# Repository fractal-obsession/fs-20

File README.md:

# FS-20

MS-20 like eurorack filter mopdule based on [KS-20](https://kassu2000.blogspot.com/2019/07/ks-20-filter.html) by _kassutronics_ based on the schematic published by René Schmitz.

Uses the LM13700 transconductance amplifier and it's buffer stage.

Includes:
 - KiCAD files for PCB and front panel
 - Custom SVGs for front panel footprints
 - JLCPCB-ready fabrication files

There are still some bugs and errors mainly on the front panel, but the electronics are correct.

[follow me](linktr.ee/fractal_obsession), or don't

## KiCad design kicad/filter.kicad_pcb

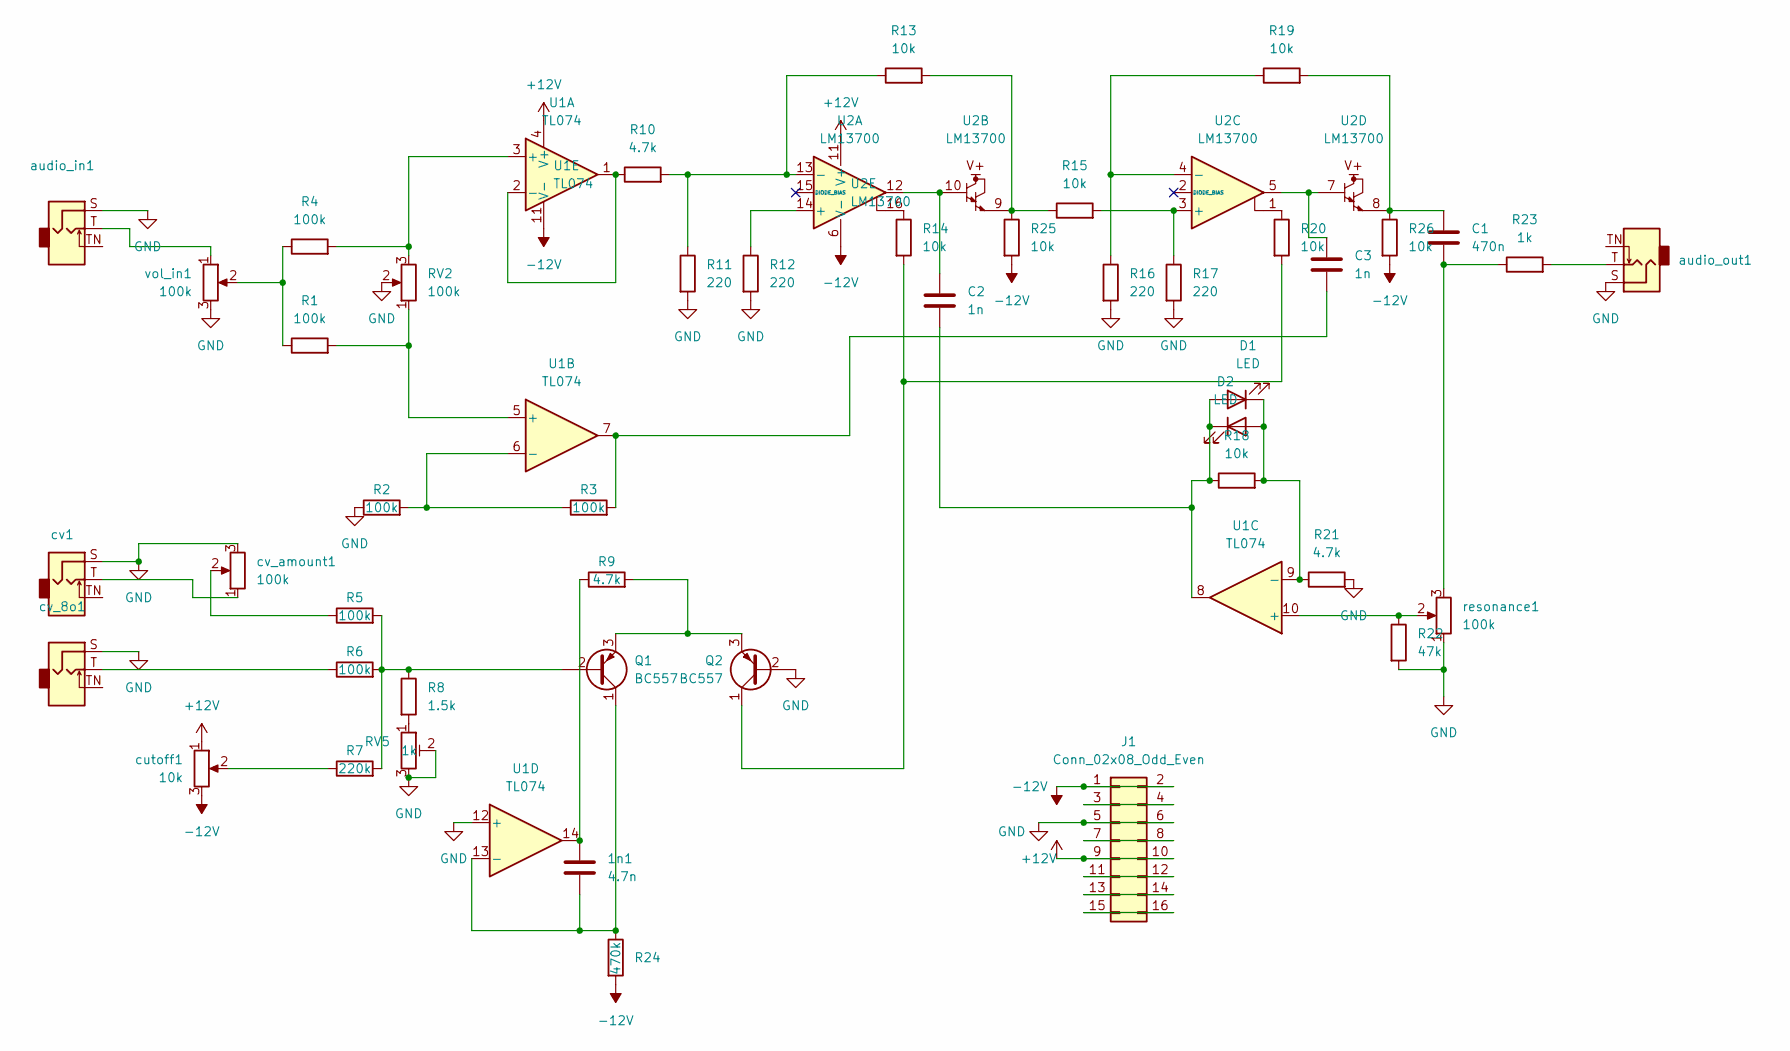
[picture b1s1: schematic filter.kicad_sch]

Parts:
1n1: 4.7n; R_Axial_DIN0207_L6.3mm_D2.5mm_P5.08mm_Vertical
C1: 470n; R_Axial_DIN0207_L6.3mm_D2.5mm_P5.08mm_Vertical
C2, C3: 1n; R_Axial_DIN0207_L6.3mm_D2.5mm_P5.08mm_Vertical
D1, D2: LED; R_Axial_DIN0207_L6.3mm_D2.5mm_P5.08mm_Vertical
J1: Conn_02x08_Odd_Even; PinHeader_2x08_P2.54mm_Vertical
Q1, Q2: BC557; TO-92_Inline
R1, R2, R3, R4, R5, R6: 100k; R_Axial_DIN0207_L6.3mm_D2.5mm_P7.62mm_Horizontal
R7: 220k; R_Axial_DIN0207_L6.3mm_D2.5mm_P7.62mm_Horizontal
R8: 1.5k; R_Axial_DIN0207_L6.3mm_D2.5mm_P7.62mm_Horizontal
R9, R10, R21: 4.7k; R_Axial_DIN0207_L6.3mm_D2.5mm_P7.62mm_Horizontal
R11, R12, R16, R17: 220; R_Axial_DIN0207_L6.3mm_D2.5mm_P7.62mm_Horizontal
R13, R14, R15, R18, R19, R20, R25, R26: 10k; R_Axial_DIN0207_L6.3mm_D2.5mm_P7.62mm_Horizontal
R22: 47k; R_Axial_DIN0207_L6.3mm_D2.5mm_P7.62mm_Horizontal
R23: 1k; R_Axial_DIN0207_L6.3mm_D2.5mm_P7.62mm_Horizontal
R24: 470k; R_Axial_DIN0207_L6.3mm_D2.5mm_P7.62mm_Horizontal
RV2: 100k; Potentiometer_Bourns_PTV09A-1_Single_Vertical
RV5: 1k; Potentiometer_Vishay_T73XX_Horizontal
U1: TL074; DIP-14_W7.62mm_Socket
U2: LM13700; DIP-16_W7.62mm_Socket
audio_in1: AudioJack2_SwitchT; Jack_3.5mm_QingPu_WQP-PJ398SM_Vertical_CircularHoles
audio_out1: AudioJack2_SwitchT; Jack_3.5mm_QingPu_WQP-PJ398SM_Vertical_CircularHoles
cutoff1: 10k; Potentiometer_Bourns_PTV09A-1_Single_Vertical
cv1: AudioJack2_SwitchT; Jack_3.5mm_QingPu_WQP-PJ398SM_Vertical_CircularHoles
cv_8o1: AudioJack2_SwitchT; Jack_3.5mm_QingPu_WQP-PJ398SM_Vertical_CircularHoles
cv_amount1: 100k; Potentiometer_Bourns_PTV09A-1_Single_Vertical
resonance1: 100k; Potentiometer_Bourns_PTV09A-1_Single_Vertical
vol_in1: 100k; Potentiometer_Bourns_PTV09A-1_Single_Vertical

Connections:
+12V: J1.9, J1.10, U1.4 (V+), U2.11 (V+), cutoff1.1
-12V: J1.1, J1.2, R24.2, R25.2, R26.2, U1.11 (V-), U2.6 (V-), cutoff1.3
GND: J1.5, J1.6, Q2.2 (B), R2.1, R11.2, R12.2, R16.2, R17.2, R21.2, R22.2, RV2.2, RV5.2, RV5.3, U1.12 (+), audio_in1.S, audio_out1.S, cv1.S, cv_8o1.S, cv_amount1.3, resonance1.1, vol_in1.3
unnamed: 1n1.1, R9.1, U1.14
unnamed: 1n1.2, Q1.1 (C), R24.1, U1.13 (-)
unnamed: C1.1, R19.2, R26.1, U2.8
unnamed: C1.2, R23.1, resonance1.3
unnamed: C2.1, U2.10, U2.12
unnamed: C2.2, D1.2 (A), D2.1 (K), R18.1, U1.8
unnamed: C3.1, U2.5, U2.7
unnamed: C3.2, R3.2, U1.7
unnamed: D1.1 (K), D2.2 (A), R18.2, R21.1, U1.9 (-)
unnamed: J1.3, J1.4
unnamed: J1.7, J1.8
unnamed: J1.11, J1.12
unnamed: J1.13, J1.14
unnamed: J1.15, J1.16
unnamed: Q1.2 (B), R5.2, R6.2, R7.2, R8.1
unnamed: Q1.3 (E), Q2.3 (E), R9.2
unnamed: Q2.1 (C), R14.2, R20.2
unnamed: R1.1, R4.1, vol_in1.2
unnamed: R1.2, RV2.1, U1.5 (+)
unnamed: R2.2, R3.1, U1.6 (-)
unnamed: R4.2, RV2.3, U1.3 (+)
unnamed: R5.1, cv_amount1.2
unnamed: R6.1, cv_8o1.T
unnamed: R7.1, cutoff1.2
unnamed: R8.2, RV5.1
unnamed: R10.1, U1.1, U1.2 (-)
unnamed: R10.2, R11.1, R13.1, U2.13 (-)
unnamed: R12.1, U2.14 (+)
unnamed: R13.2, R15.1, R25.1, U2.9
unnamed: R14.1, U2.16
unnamed: R15.2, R17.1, U2.3 (+)
unnamed: R16.1, R19.1, U2.4 (-)
unnamed: R20.1, U2.1
unnamed: R22.1, U1.10 (+), resonance1.2
unnamed: R23.2, audio_out1.T
unnamed: audio_in1.T, vol_in1.1
unnamed: cv1.T, cv_amount1.1

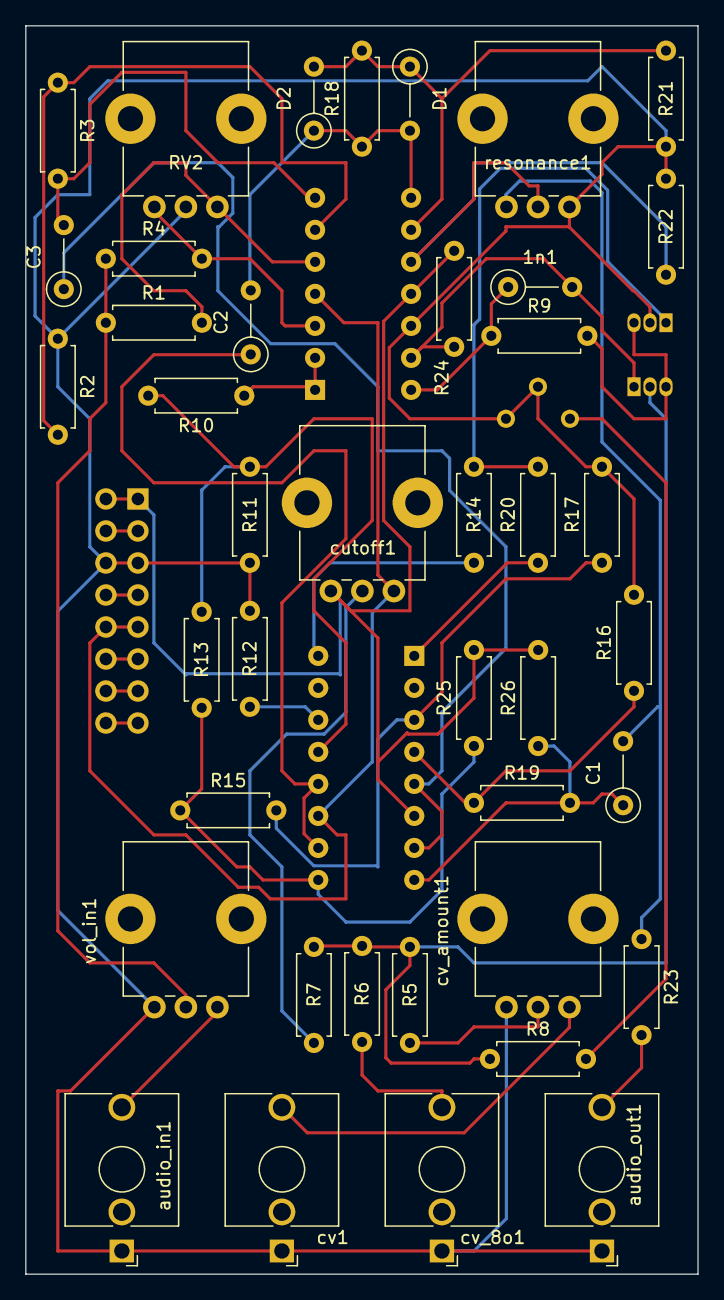
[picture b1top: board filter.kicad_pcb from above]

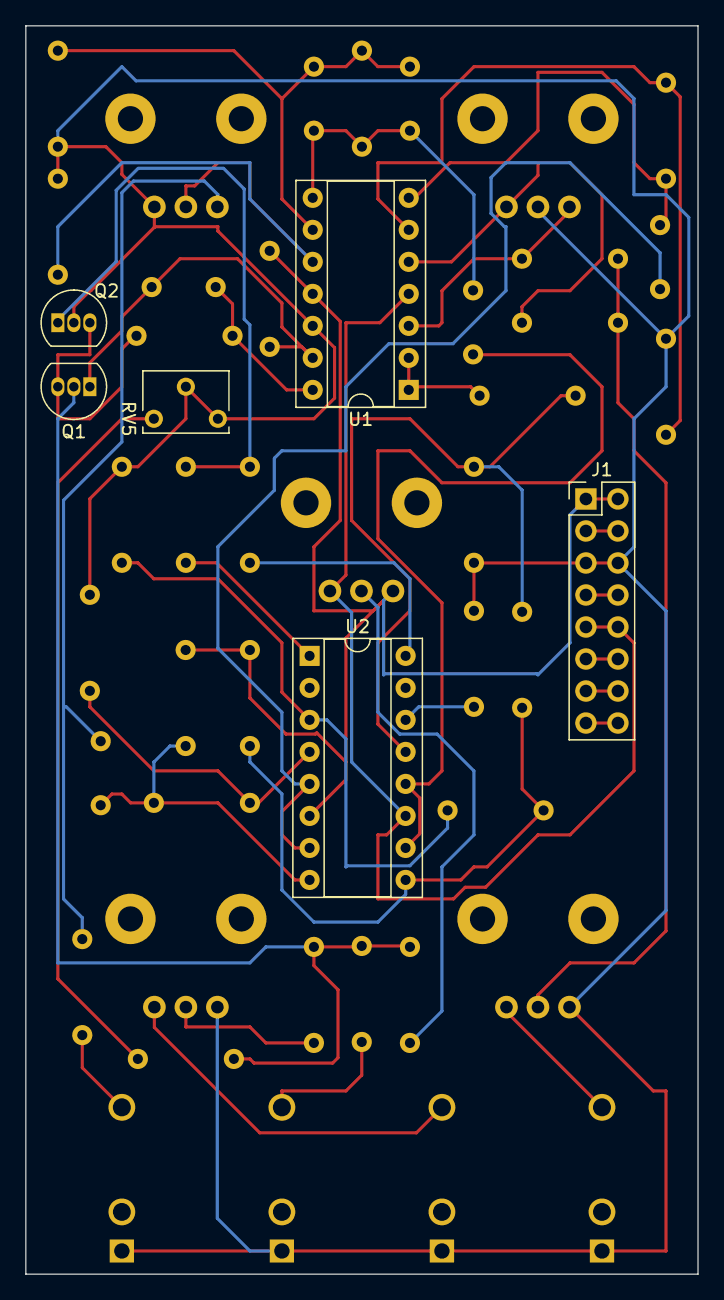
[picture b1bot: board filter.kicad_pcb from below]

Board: 2 copper layers, 53.3 x 99.1 mm, 47 parts (6 on the bottom side), 40 nets.
